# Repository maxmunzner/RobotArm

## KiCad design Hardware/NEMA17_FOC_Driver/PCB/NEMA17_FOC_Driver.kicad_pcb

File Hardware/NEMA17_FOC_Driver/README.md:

# NEMA17_FOC_Driver
A Stepper Driver project with a PCB that acts as the driver and encoder.

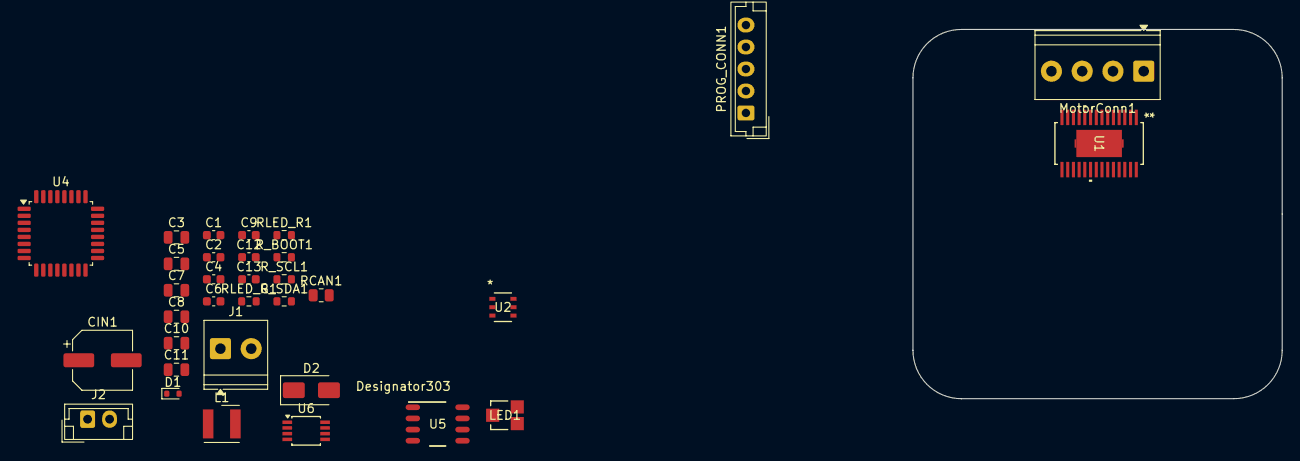
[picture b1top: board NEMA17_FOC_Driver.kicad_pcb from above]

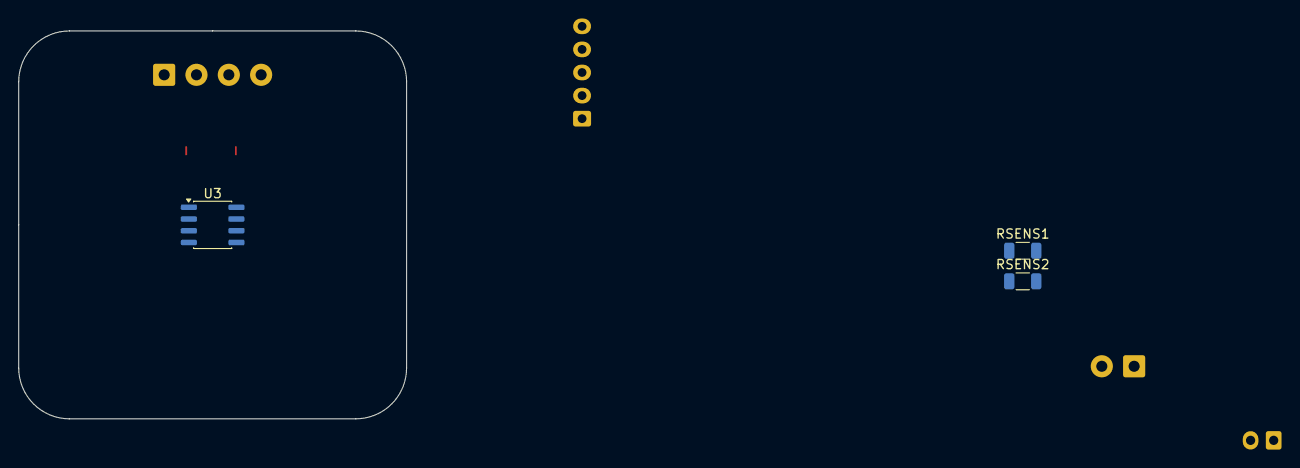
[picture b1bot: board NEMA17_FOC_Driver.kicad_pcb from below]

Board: 2 copper layers, 42.0 x 42.0 mm, 36 parts (3 on the bottom side), 38 nets, no tracks yet.

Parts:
C1, C2, C9: 0.1u; C_0603_1608Metric
C3, C5, C10, C11: 10u; C_0805_2012Metric
C4: 0.47u; C_0603_1608Metric
C6, C12, C13: 100n; C_0603_1608Metric
C7, C8: 22u; C_0805_2012Metric
CIN1: 100u; CP_Elec_6.3x7.7
D1: ESD5Zxx; D_SOD-523
D2: SMAJ18A; D_SMA
J1: Conn_01x02_Pin; TerminalBlock_Phoenix_PT-1,5-2-3.5-H_1x02_P3.50mm_Horizontal
J2: Conn_01x02_Pin; JST_EH_B2B-EH-A_1x02_P2.50mm_Vertical
L1: 3.9u; L_Wurth_WE-LQSH-4020
LED1: SML-LX15IGC-RT-TR; SML-LX15_LUM
MotorConn1: TerminalBlock_Phoenix_PT-1,5-4-3.5-H_1x04_P3.50mm_Horizontal
PROG_CONN1: Conn_01x05_Pin; JST_EH_B5B-EH-A_1x05_P2.50mm_Vertical
RCAN1: 120; R_0805_2012Metric
RLED_G1: 220; R_0603_1608Metric
RLED_R1: 220; R_0603_1608Metric
RSENS1, RSENS2: 0.1; R_1206_3216Metric
R_BOOT1: 10k; R_0603_1608Metric
R_SCL1: 10k; R_0603_1608Metric
R_SDA1: 10k; R_0603_1608Metric
U1: DRV8844PWPR; PWP28_5P18X3P1-M
U2: AP63203WU-7; AP63203WU-7_DIO-L
U3: MT6701CT; SO-8_3.9x4.9mm_P1.27mm
U4: STM32G431KBTx; LQFP-32_7x7mm_P0.8mm
U5: TCAN332; D0008A_M
U6: 24LC64; TSSOP-8_3x3mm_P0.65mm

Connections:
+3.3V: C7.1, C8.1, C9.1, C10.1, C11.1, C12.1, C13.1, D1.1 (K), L1.2, PROG_CONN1.1, R_SCL1.1, R_SDA1.1, U2.1 (FB), U3.1 (VDD), U3.2 (MODE), U4.1 (VDD), U4.15 (VDDA), U4.17 (VDD), U5.3 (VCC), U6.8 (VCC)
+12V: C2.1, C3.1, C5.1, CIN1.1, D2.1 (A1), J1.1, U1.4 (VM), U1.11 (VM), U2.2 (EN), U2.3 (VIN)
CAN High: J2.2, RCAN1.2, U5.7 (CANH)
CAN Low: J2.1, RCAN1.1, U5.6 (CANL)
ChipSelect: U3.8 (Z), U4.28 (PB5)
Clock: U3.7 (B), U4.26 (PB3)
DataOut: U3.6 (A), U4.27 (PB4)
EN: U1.20 (EN4), U1.22 (EN3), U1.24 (EN2), U1.26 (EN1), U4.2 (PF0)
GND: C3.2, C4.1, C5.2, C7.2, C8.2, C9.2, C10.2, C11.2, C12.2, C13.2, CIN1.2, D1.2 (A), D2.2 (A2), J1.2, LED1.3, PROG_CONN1.3, RSENS1.2, RSENS2.2, R_BOOT1.2, U1.14 (VNEG), U1.19 (LGND), U1.28 (VNEG), U1.29 (EPAD), U2.4 (GND), U3.4 (GND), U4.14 (VSSA), U4.16 (VSS), U4.32 (VSS), U5.2 (GND), U6.4 (GND), U6.7 (WP)
IN1: U1.27 (IN1), U4.18 (PA8)
IN2: U1.25 (IN2), U4.19 (PA9)
IN3: U1.23 (IN3), U4.20 (PA10)
IN4: U1.21 (IN4), U4.21 (PA11)
LEDPIN_G: RLED_G1.2, U4.7 (PA2)
LEDPIN_R: RLED_R1.1, U4.8 (PA3)
NRST: PROG_CONN1.5, U4.4 (PG10)
unnamed: LED1.1, RLED_R1.2
unnamed: LED1.2, RLED_G1.1
unnamed: MotorConn1.1, U1.5 (OUT1)
unnamed: MotorConn1.2, U1.7 (OUT2)
unnamed: MotorConn1.3, U1.8 (OUT3)
unnamed: MotorConn1.4, U1.10 (OUT4)
unnamed: C1.2, U1.1 (CP1)
unnamed: C1.1, U1.2 (CP2)
unnamed: C4.2, U1.15 (V3P3OUT)
unnamed: C2.2, U1.3 (VCP)
unnamed: C6.1, U2.6 (BST)
unnamed: C6.2, L1.1, U2.5 (SW)
RXD: R_BOOT1.1, U4.31 (PB8), U5.4 (RXD)
SCL: R_SCL1.2, U4.25 (PA15), U6.6 (SCL)
SDA: R_SDA1.2, U4.30 (PB7), U6.5 (SDA)
SRC12: RSENS1.1, U1.6 (VNEG), U4.6 (PA1)
SRC34: RSENS2.1, U1.9 (VNEG), U4.12 (PA7)
SWCLK: PROG_CONN1.2, U4.24 (PA14)
SWDIO: PROG_CONN1.4, U4.23 (PA13)
TXD: U4.22 (PA12), U5.1 (TXD)
nFAULT: U1.18 (NFAULT), U4.5 (PA0)
nRESET: U1.16 (NRESET), U1.17 (NSLEEP), U4.3 (PF1)

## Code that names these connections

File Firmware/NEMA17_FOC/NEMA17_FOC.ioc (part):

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Mcu.Name=STM32G431K(6-8-B)Tx
Mcu.Package=LQFP32
Mcu.UserName=STM32G431KBTx
PA1.Mode=PGA_Internally_Connected
PA1.Signal=OPAMP1_VINP
PA10.Signal=S_TIM1_CH3
PA11.Signal=S_TIM1_CH4
PA12.Mode=FDCAN_Activate
PA12.Signal=FDCAN1_TX
PA13.Mode=Serial_Wire
PA13.Signal=SYS_JTMS-SWDIO
PA14.Mode=Serial_Wire
PA14.Signal=SYS_JTCK-SWCLK
PA15.Mode=I2C
PA15.Signal=I2C1_SCL
PA2.Signal=GPIO_Output
PA3.Signal=GPIO_Output
PA4.Signal=GPIO_Output
PA5.Mode=RX_Only_Simplex_Unidirect_Master
PA5.Signal=SPI1_SCK
PA6.Mode=RX_Only_Simplex_Unidirect_Master
PA6.Signal=SPI1_MISO
PA7.Mode=PGA_Internally_Connected
PA7.Signal=OPAMP2_VINP
PA8.Signal=S_TIM1_CH1
PA9.Signal=S_TIM1_CH2
PB3.Signal=GPIO_Input
PB4.Signal=GPIO_Output
PB5.Signal=GPIO_Output
PB7.Mode=I2C
PB7.Signal=I2C1_SDA
PB8-BOOT0.Mode=FDCAN_Activate
PB8-BOOT0.Signal=FDCAN1_RX
RCC.HSE_VALUE=8000000
RCC.SYSCLKFreq_VALUE=16000000
board=custom

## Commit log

2026-02-06 Initial commit with project structure
2026-02-23 Firmware base project structure and config file
2026-04-10 Firmware structure, schematic for PCB V2.0, layout still pending.
